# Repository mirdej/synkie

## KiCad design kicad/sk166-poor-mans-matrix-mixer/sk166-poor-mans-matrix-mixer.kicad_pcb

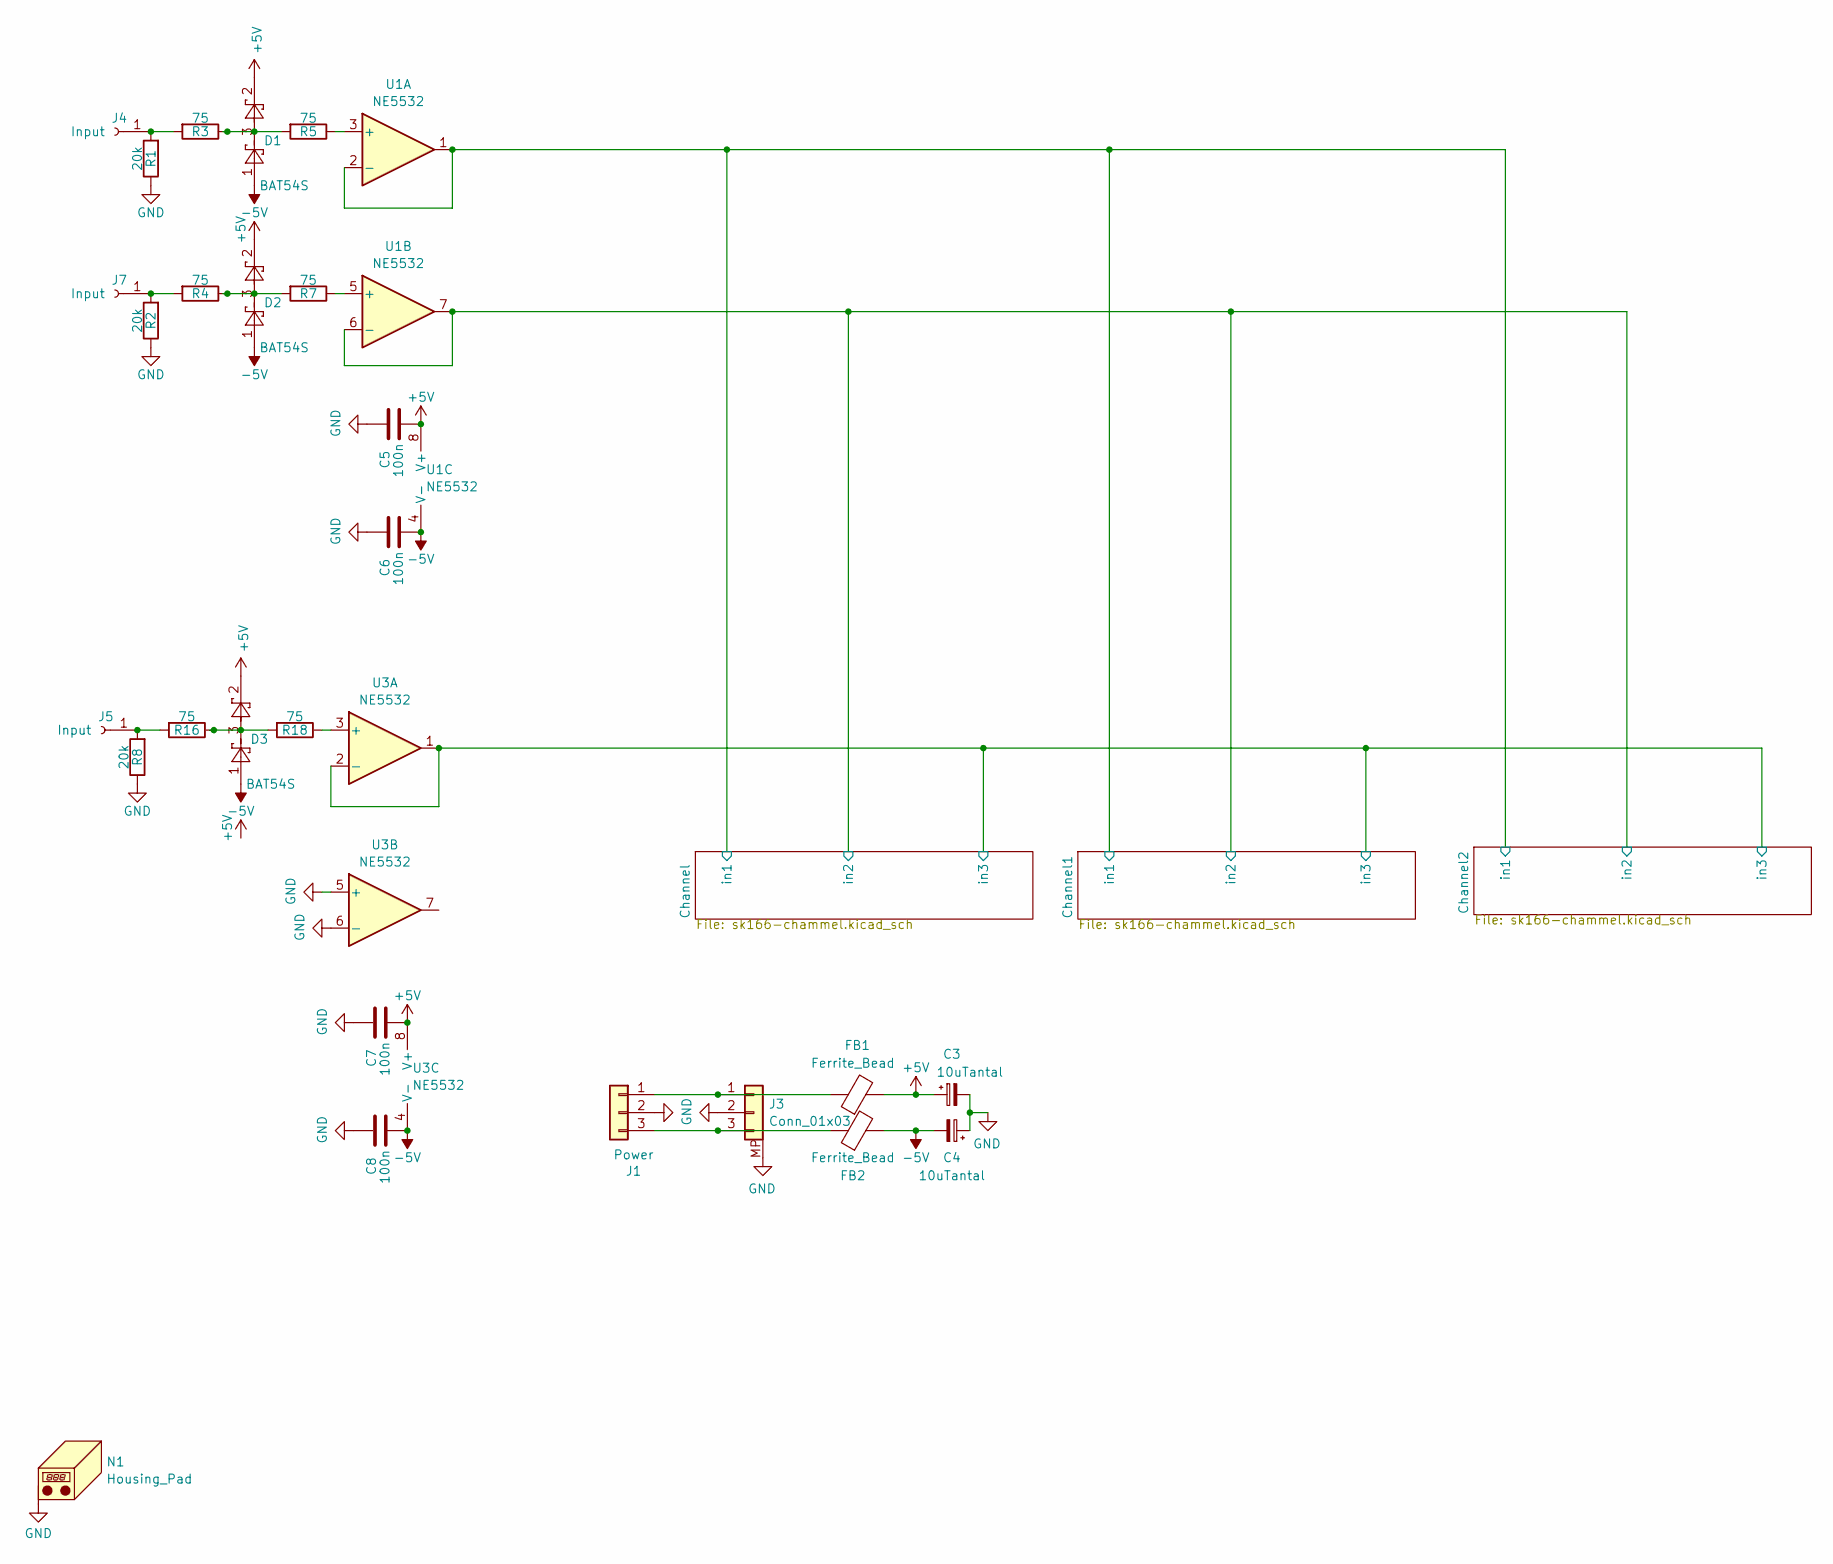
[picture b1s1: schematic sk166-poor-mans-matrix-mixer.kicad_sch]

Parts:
C3, C4: 10uTantal; CP_EIA-3216-18_Kemet-A; LCSC C7171
C5, C6, C7, C8: 100n; C_0603_1608Metric; LCSC C14663
D1, D2, D3: BAT54S; SOT-23; LCSC C7420333
FB1, FB2: Ferrite_Bead; L_0805_2012Metric; LCSC C1017
J1: Power; Molex_KK-254_AE-6410-03A_1x03_P2.54mm_Vertical_SMD
J3: Conn_01x03; Molex_PicoBlade_53398-0371_1x03-1MP_P1.25mm_Vertical; LCSC C293633
J4, J5, J7: Input; Banana2mm-Löthülse
N1: Housing_Pad; Frontplate_40mm
R1, R2, R8: 20k; R_0603_1608Metric; LCSC C4184
R3, R4, R5, R7, R16, R18: 75; R_0603_1608Metric; LCSC C4275
U1, U3: NE5532; SOIC-8_3.9x4.9mm_P1.27mm; LCSC C7426

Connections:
+5V: C3.1, C5.2, C7.2, D1.2, D2.2, D3.2, FB1.2, U1.8 (V+), U3.8 (V+); also elsewhere on the board
-5V: C4.2, C6.2, C8.2, D1.1, D2.1, D3.1, FB2.2, U1.4 (V-), U3.4 (V-); also elsewhere on the board
/Channel/in1: U1.1, U1.2 (-); also elsewhere on the board
/Channel/in2: U1.6 (-), U1.7; also elsewhere on the board
/Channel/in3: U3.1, U3.2 (-); also elsewhere on the board
GND: C3.2, C4.1, C5.1, C6.1, C7.1, C8.1, J1.2, J3.2, J3.MP, N1.1 (PAD_1), R1.1, R2.1, R8.1, U3.5 (+), U3.6 (-); also elsewhere on the board
unnamed: D1.3, R3.1, R5.2
unnamed: D2.3, R4.1, R7.2
unnamed: D3.3, R16.1, R18.2
unnamed: FB1.1, J1.1, J3.1
unnamed: FB2.1, J1.3, J3.3
unnamed: J4.1 (Pin_1_1), R1.2, R3.2
unnamed: J5.1 (Pin_1_1), R8.2, R16.2
unnamed: J7.1 (Pin_1_1), R2.2, R4.2
unnamed: R5.1, U1.3 (+)
unnamed: R7.1, U1.5 (+)
unnamed: R18.1, U3.3 (+)

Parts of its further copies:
C12: 100n; C_0603_1608Metric; LCSC C14663
R26: 75; R_0603_1608Metric; LCSC C4275

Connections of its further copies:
-5V: C12.2; also elsewhere on the board
GND: C12.1; also elsewhere on the board
unnamed 14: R26.1; also elsewhere on the board
unnamed 26: R26.2; also elsewhere on the board

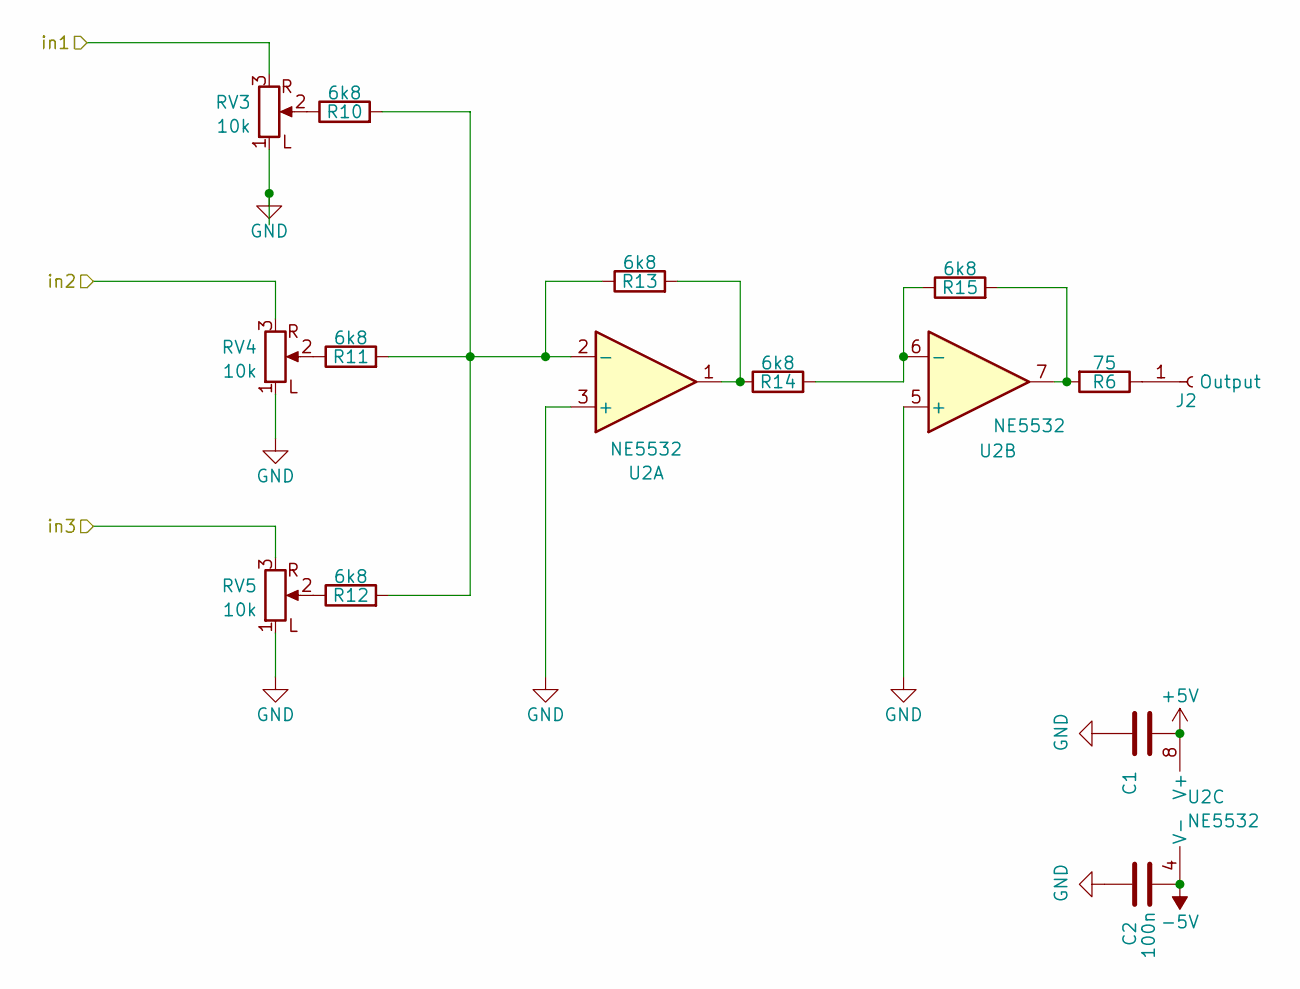
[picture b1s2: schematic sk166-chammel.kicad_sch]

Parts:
C1, C2: 100n; C_0402_1005Metric; LCSC C1525
J2: Output; Banana2mm-Löthülse
R6: 75; R_0603_1608Metric; LCSC C4275
R10, R11, R12, R13, R14, R15: 6k8; R_0603_1608Metric; LCSC C23212
RV3, RV4, RV5: 10k; Alps_RK097_Frontplate; LCSC C115340
U2: NE5532; SOIC-8_3.9x4.9mm_P1.27mm; LCSC C7426

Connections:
+5V: C1.2, U2.8 (V+); also elsewhere on the board
-5V: C2.2, U2.4 (V-); also elsewhere on the board
/Channel/in1: RV3.3; also elsewhere on the board
/Channel/in2: RV4.3; also elsewhere on the board
/Channel/in3: RV5.3; also elsewhere on the board
GND: C1.1, C2.1, RV3.1 (L), RV4.1 (L), RV5.1 (L), U2.3 (+), U2.5 (+); also elsewhere on the board
unnamed: J2.1 (Pin_1_1), R6.1
unnamed: R10.1, RV3.2
unnamed: R11.1, RV4.2
unnamed: R12.1, RV5.2
unnamed: R13.2, R14.1, U2.1
unnamed: R6.2, R15.2, U2.7
unnamed: R10.2, R11.2, R12.2, R13.1, U2.2 (-)
unnamed: R14.2, R15.1, U2.6 (-)

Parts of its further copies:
C9, C10, C11, C12: 100n; C_0402_1005Metric; LCSC C1525
J6, J9: Output; Banana2mm-Löthülse
R20, R21, R22, R23, R24, R25, R27, R28, R29, R30, R31, R32: 6k8; R_0603_1608Metric; LCSC C23212
R26, R33: 75; R_0603_1608Metric; LCSC C4275
RV6, RV7, RV8, RV9, RV10, RV11: 10k; Alps_RK097_Frontplate; LCSC C115340
U4, U5: NE5532; SOIC-8_3.9x4.9mm_P1.27mm; LCSC C7426

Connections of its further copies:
+5V: C9.2, C11.2, U4.8 (V+), U5.8 (V+); also elsewhere on the board
-5V: C10.2, C12.2, U4.4 (V-), U5.4 (V-); also elsewhere on the board
/Channel/in1: RV6.3, RV9.3; also elsewhere on the board
/Channel/in2: RV7.3, RV10.3; also elsewhere on the board
/Channel/in3: RV8.3, RV11.3; also elsewhere on the board
GND: C9.1, C10.1, C11.1, C12.1, RV6.1 (L), RV7.1 (L), RV8.1 (L), RV9.1 (L), RV10.1 (L), RV11.1 (L), U4.3 (+), U4.5 (+), U5.3 (+), U5.5 (+); also elsewhere on the board
unnamed: J6.1 (Pin_1_1), R26.1
unnamed: J9.1 (Pin_1_1), R33.1
unnamed: R20.1, RV6.2
unnamed: R21.1, RV7.2
unnamed: R22.1, RV8.2
unnamed: R23.2, R24.1, U4.1
unnamed: R25.2, R26.2, U4.7
unnamed: R27.1, RV9.2
unnamed: R28.1, RV10.2
unnamed: R29.1, RV11.2
unnamed: R30.2, R31.1, U5.1
unnamed: R32.2, R33.2, U5.7
unnamed: R20.2, R21.2, R22.2, R23.1, U4.2 (-)
unnamed: R24.2, R25.1, U4.6 (-)
unnamed: R27.2, R28.2, R29.2, R30.1, U5.2 (-)
unnamed: R31.2, R32.1, U5.6 (-)

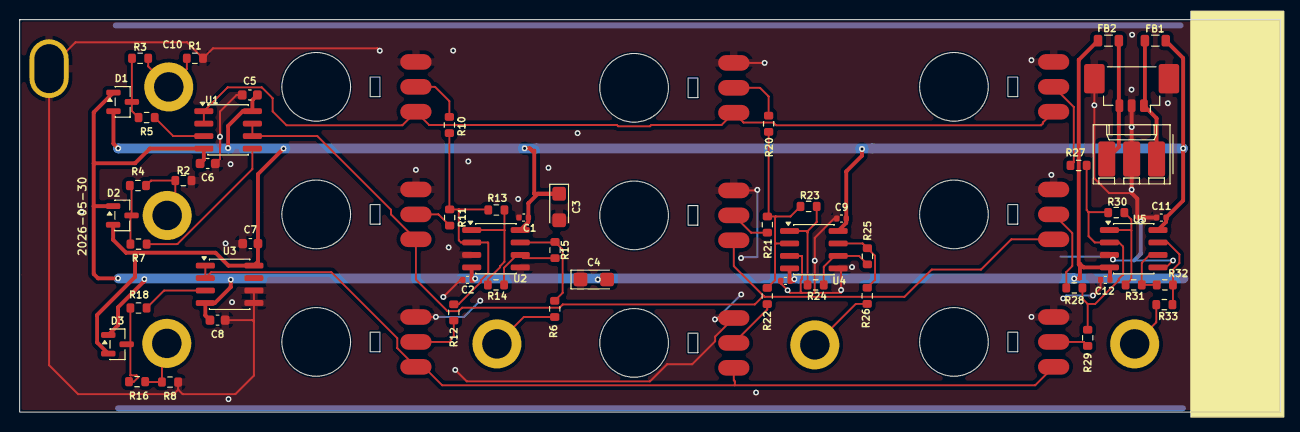
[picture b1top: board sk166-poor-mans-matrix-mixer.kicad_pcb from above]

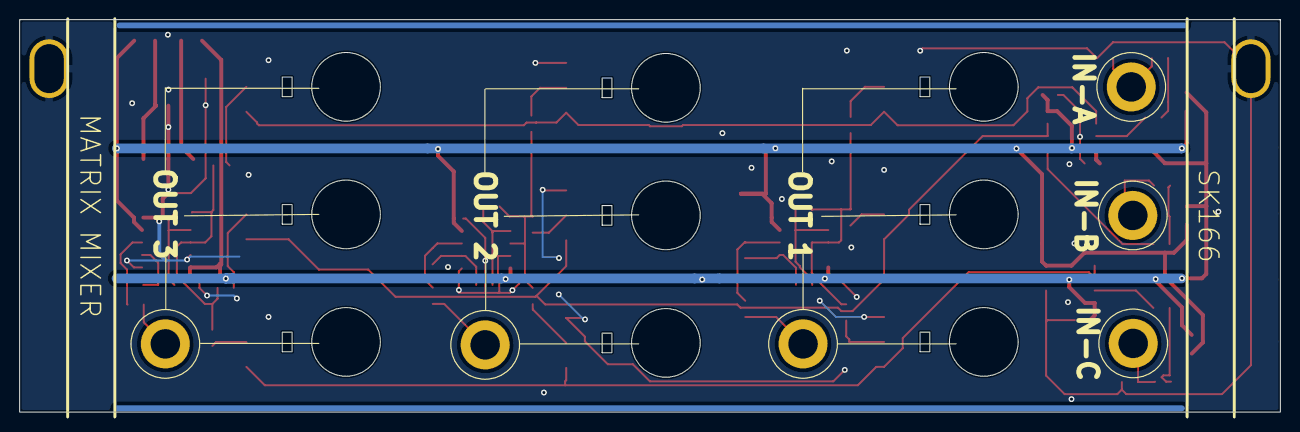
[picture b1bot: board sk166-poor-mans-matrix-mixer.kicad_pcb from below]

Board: 2 copper layers, 128.5 x 40.0 mm, 70 parts (16 on the bottom side), 41 nets.

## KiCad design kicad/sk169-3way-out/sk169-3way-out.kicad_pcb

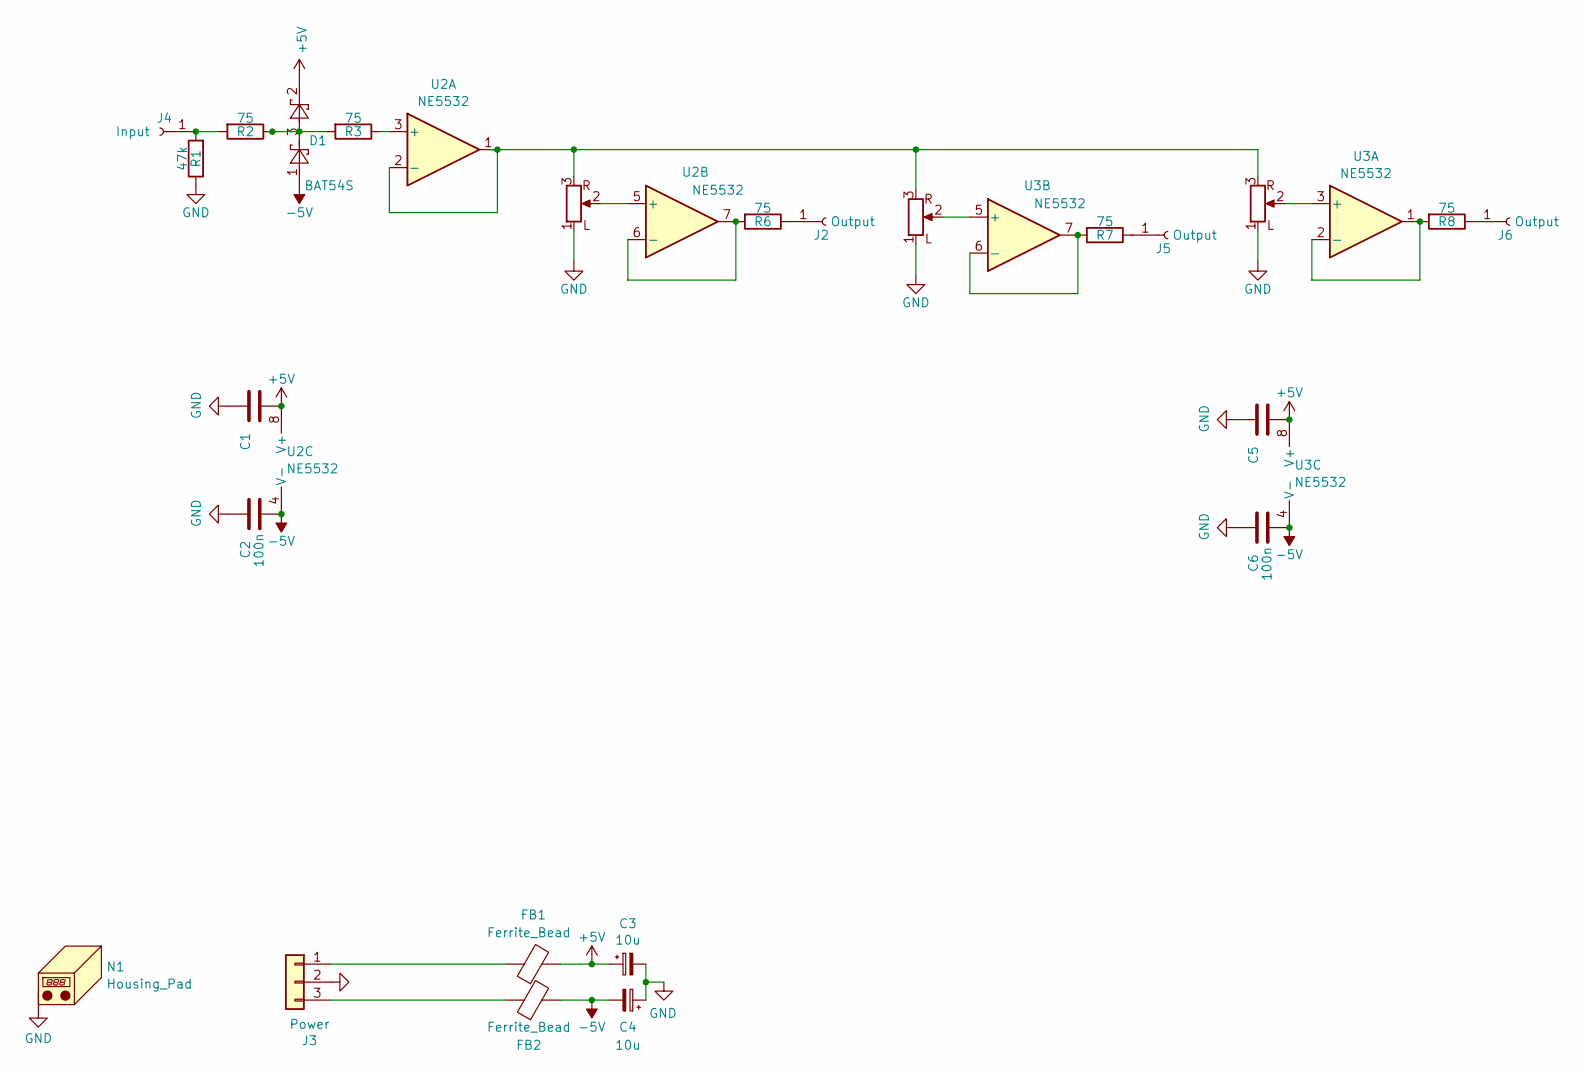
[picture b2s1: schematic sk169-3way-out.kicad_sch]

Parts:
C1, C2, C5, C6: 100n; C_0402_1005Metric; LCSC C1525
C3, C4: 10u; C_0805_2012Metric; LCSC C15850
D1: BAT54S; SOT-23; LCSC C8592
FB1, FB2: Ferrite_Bead; L_0805_2012Metric; LCSC C1017
J2, J5, J6: Output; Banana2mm-Löthülse
J3: Power; Molex_KK-254_AE-6410-03A_1x03_P2.54mm_Vertical_SMD
J4: Input; Banana2mm-Löthülse
N1: Housing_Pad; Frontplate_10mm
R1: 47k; R_0603_1608Metric; LCSC C25819
R2, R3, R6, R7, R8: 75; R_0603_1608Metric; LCSC C4275
RV3, RV4, RV5: 10k; Alps_RK097_Frontplate
U2, U3: NE5532; SOIC-8_3.9x4.9mm_P1.27mm; LCSC C7426

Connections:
+5V: C1.2, C3.1, C5.2, D1.2, FB1.2, U2.8 (V+), U3.8 (V+)
-5V: C2.2, C4.2, C6.2, D1.1, FB2.2, U2.4 (V-), U3.4 (V-)
GND: C1.1, C2.1, C3.2, C4.1, C5.1, C6.1, J3.2, N1.1 (PAD_1), R1.1, RV3.1 (L), RV4.1 (L), RV5.1 (L)
unnamed: D1.3, R2.1, R3.2
unnamed: J2.1 (Pin_1_1), R6.1
unnamed: FB1.1, J3.1
unnamed: FB2.1, J3.3
unnamed: J4.1 (Pin_1_1), R1.2, R2.2
unnamed: J5.1 (Pin_1_1), R7.1
unnamed: J6.1 (Pin_1_1), R8.1
unnamed: R3.1, U2.3 (+)
unnamed: RV3.3, RV4.3, RV5.3, U2.1, U2.2 (-)
unnamed: RV3.2, U2.5 (+)
unnamed: R6.2, U2.6 (-), U2.7
unnamed: RV5.2, U3.3 (+)
unnamed: R8.2, U3.1, U3.2 (-)
unnamed: RV4.2, U3.5 (+)
unnamed: R7.2, U3.6 (-), U3.7

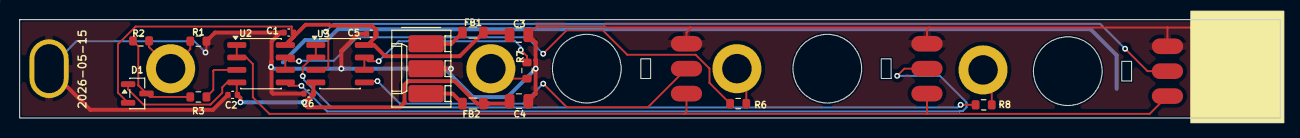
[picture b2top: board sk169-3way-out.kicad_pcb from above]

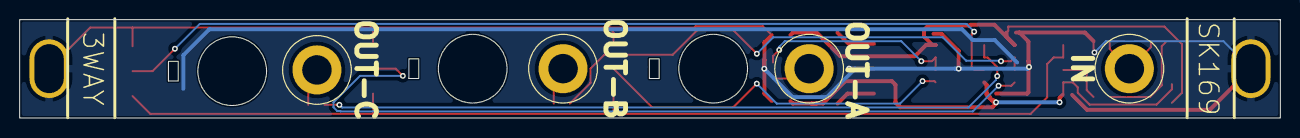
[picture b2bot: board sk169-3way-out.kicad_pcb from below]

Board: 2 copper layers, 128.5 x 10.0 mm, 26 parts (8 on the bottom side), 18 nets.

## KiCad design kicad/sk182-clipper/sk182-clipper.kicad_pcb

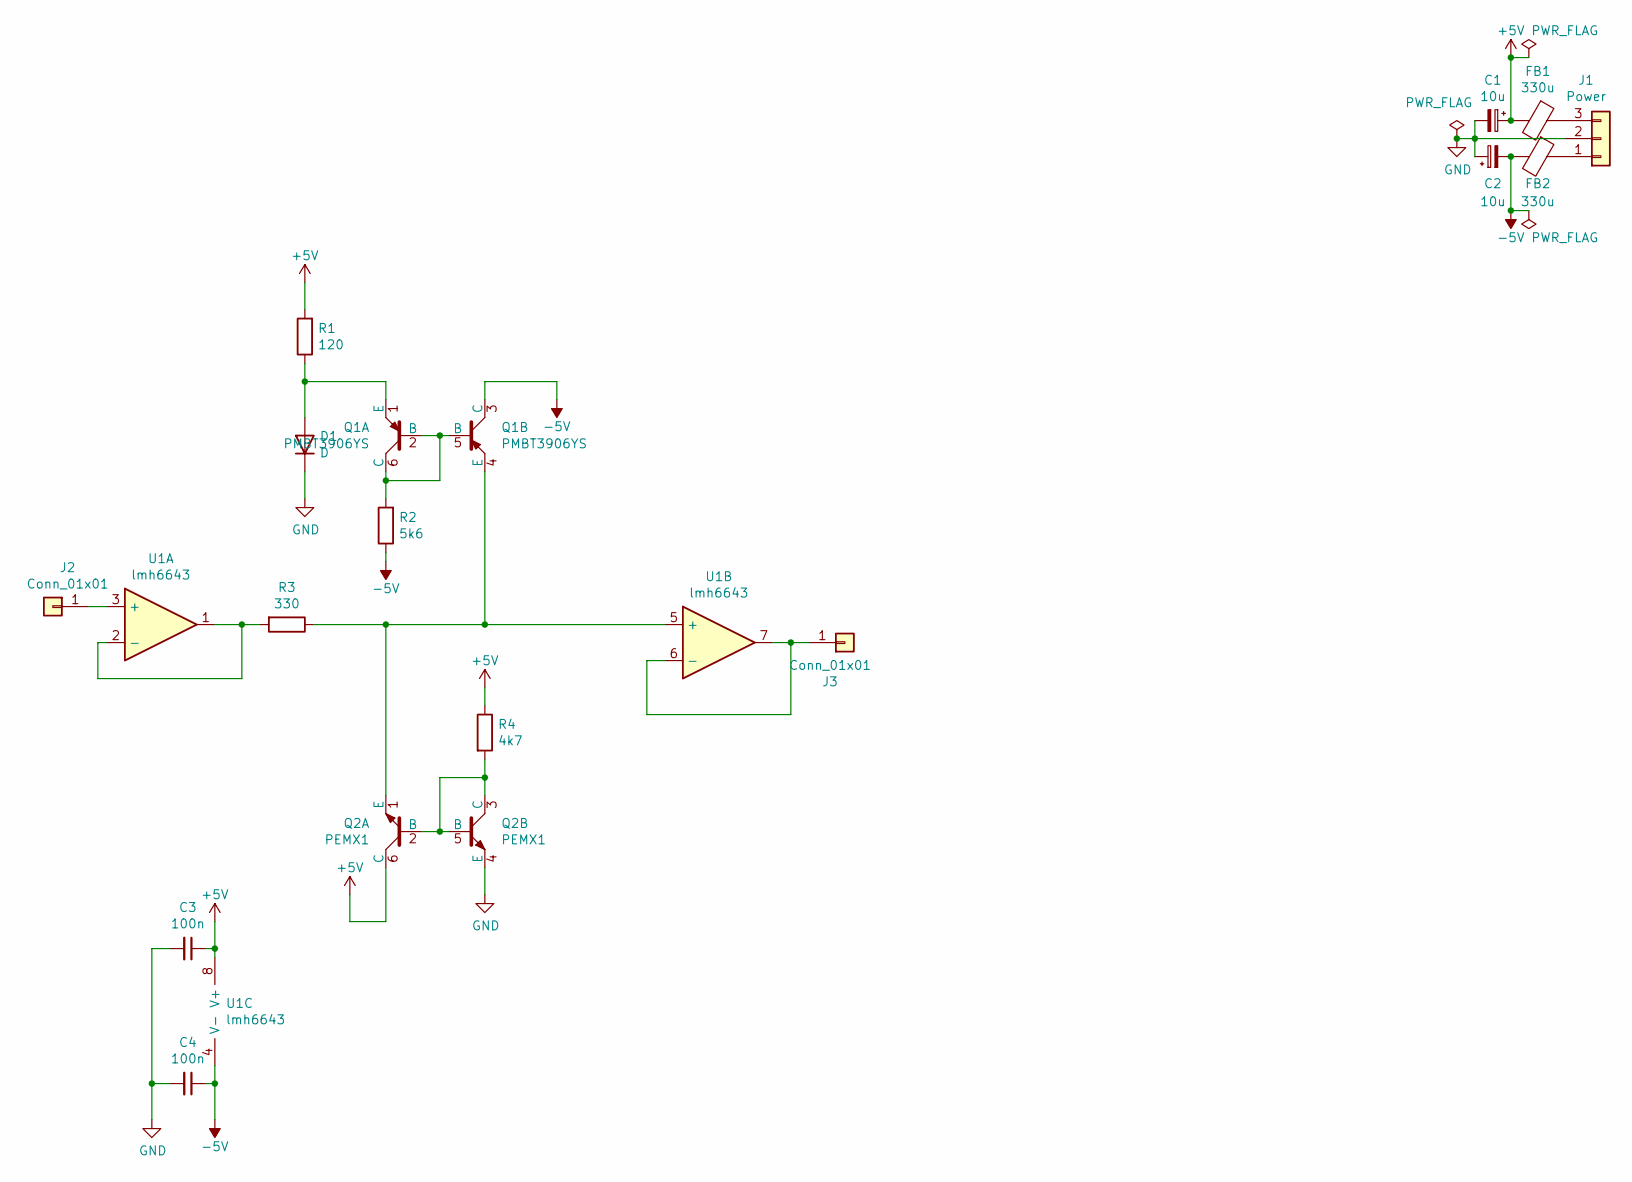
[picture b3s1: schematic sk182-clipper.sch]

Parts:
C1, C2: 10u; CP_EIA-3528-21_Kemet-B_Pad1.50x2.35mm_HandSolder
C3, C4: 100n; C_0805_2012Metric_Pad1.15x1.40mm_HandSolder
D1: D; D_MiniMELF_Handsoldering
FB1, FB2: 330u; L_1206_3216Metric_Pad1.42x1.75mm_HandSolder
J1: Power; Molex_KK-254_AE-6410-03A_1x03_P2.54mm_Vertical
J2, J3: Conn_01x01; Solderpad_1mm
Q1: PMBT3906YS; SOT-363_SC-70-6_Handsoldering
Q2: PEMX1; SOT-666
R1: 120; R_0805_2012Metric_Pad1.15x1.40mm_HandSolder
R2: 5k6; R_0805_2012Metric_Pad1.15x1.40mm_HandSolder
R3: 330; R_0805_2012Metric_Pad1.15x1.40mm_HandSolder
R4: 4k7; R_0805_2012Metric_Pad1.15x1.40mm_HandSolder
U1: lmh6643; SOIC-8_3.9x4.9mm_P1.27mm

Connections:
+5V: C1.1, C3.1, FB1.2, Q2.6 (C), R1.2, R4.1, U1.8 (V+)
-5V: C2.2, C4.1, FB2.2, Q1.3 (C), R2.1, U1.4 (V-)
GND: C1.2, C2.1, C3.2, C4.2, D1.1 (K), J1.2, Q2.4 (E); also elsewhere on the board
unnamed: D1.2 (A), Q1.1 (E), R1.1
unnamed 4: Q2.2 (B), Q2.3 (C), Q2.5 (B), R4.2; also elsewhere on the board
unnamed: FB1.1, J1.3
unnamed: FB2.1, J1.1
unnamed: J2.1, U1.3 (+)
unnamed: J3.1, U1.6 (-), U1.7
unnamed: Q1.2 (B), Q1.5 (B), Q1.6 (C), R2.2
unnamed: Q1.4 (E), Q2.1 (E), R3.1, U1.5 (+)
unnamed: R3.2, U1.1, U1.2 (-)

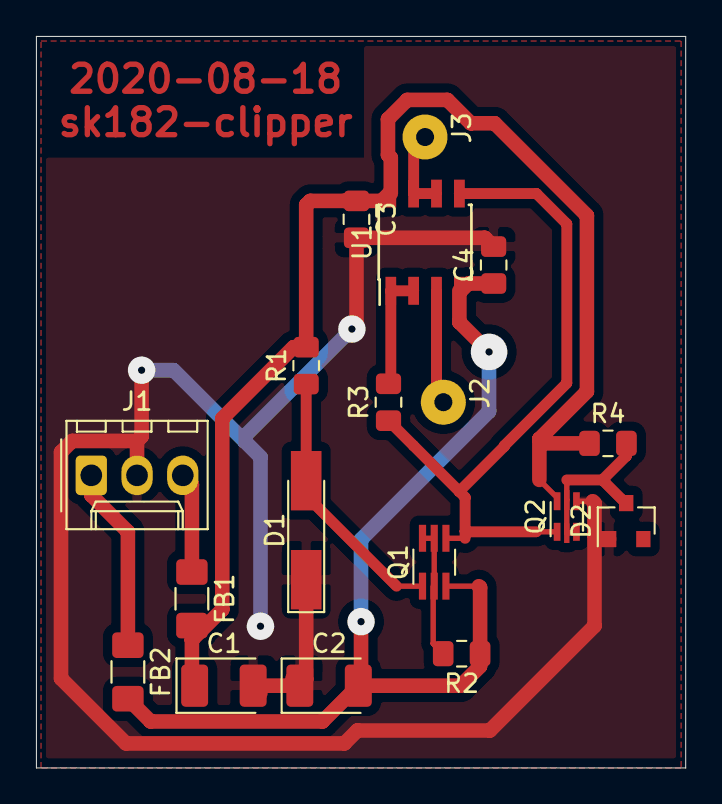
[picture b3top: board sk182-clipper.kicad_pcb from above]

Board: 2 copper layers, 36.1 x 40.6 mm, 18 parts (0 on the bottom side), 12 nets.

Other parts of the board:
D2: BAT54; D_SOT-23_ANK

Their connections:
GND: D2.2; also elsewhere on the board
unnamed 4: D2.1; also elsewhere on the board

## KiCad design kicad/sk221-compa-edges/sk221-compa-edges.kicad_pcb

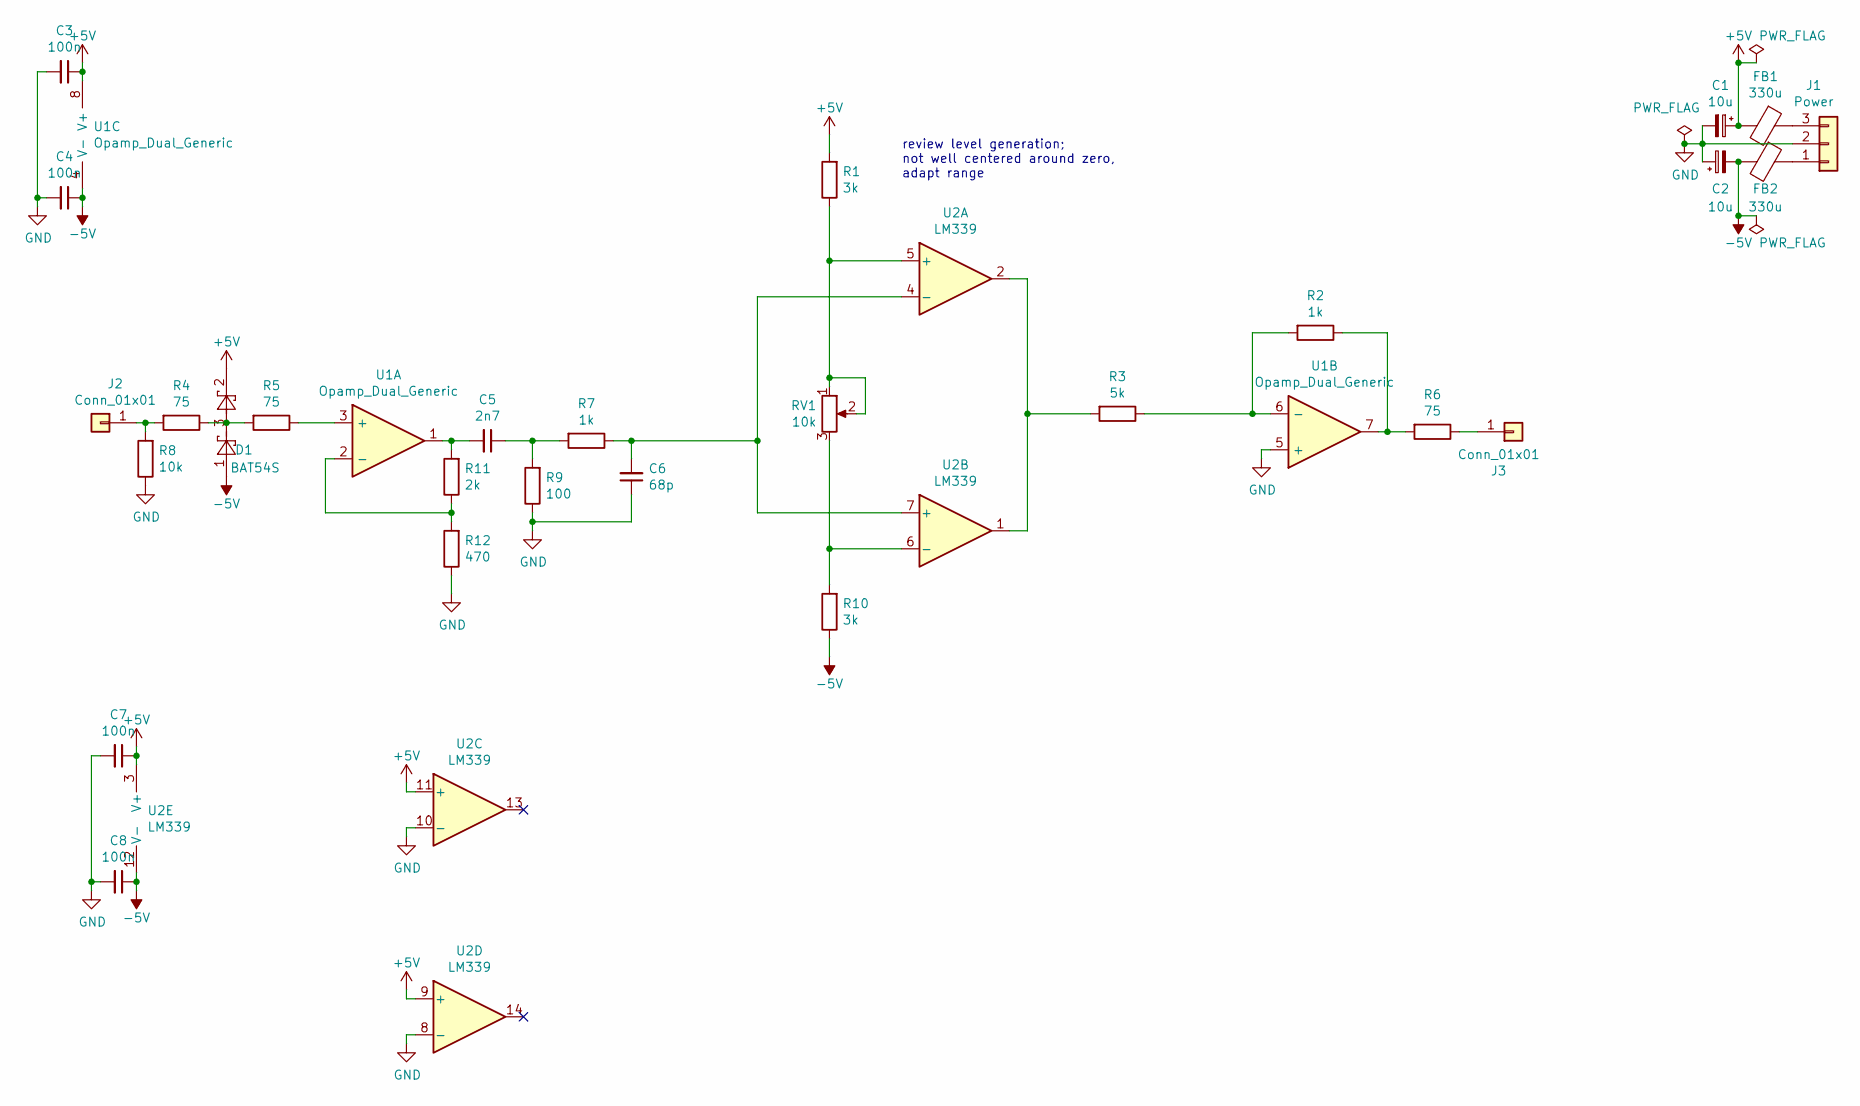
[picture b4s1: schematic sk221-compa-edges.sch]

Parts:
C1, C2: 10u; CP_EIA-3528-21_Kemet-B_Pad1.50x2.35mm_HandSolder
C3, C4, C7, C8: 100n; C_0603_1608Metric_Pad1.05x0.95mm_HandSolder
C5: 2n7; C_0805_2012Metric_Pad1.15x1.40mm_HandSolder
C6: 68p; C_0805_2012Metric_Pad1.15x1.40mm_HandSolder
D1: BAT54S; SOT-23
FB1, FB2: 330u; L_1206_3216Metric_Pad1.42x1.75mm_HandSolder
J1: Power; Molex_KK-254_AE-6410-03A_1x03_P2.54mm_Vertical
J2, J3: Conn_01x01; Solderpad_1mm
R1, R10: 3k; R_0805_2012Metric_Pad1.15x1.40mm_HandSolder
R2, R7: 1k; R_0805_2012Metric_Pad1.15x1.40mm_HandSolder
R3: 5k; R_0805_2012Metric_Pad1.15x1.40mm_HandSolder
R4, R5, R6: 75; R_0805_2012Metric_Pad1.15x1.40mm_HandSolder
R8: 10k; R_0805_2012Metric_Pad1.15x1.40mm_HandSolder
R9: 100; R_0805_2012Metric_Pad1.15x1.40mm_HandSolder
R11: 2k; R_0805_2012Metric_Pad1.15x1.40mm_HandSolder
R12: 470; R_0805_2012Metric_Pad1.15x1.40mm_HandSolder
RV1: 10k; Potentiometer_Alps_RK09Y11_Single_Horizontal
U1: Opamp_Dual_Generic; SOIC-8_3.9x4.9mm_P1.27mm
U2: LM339; SOIC-14_3.9x8.7mm_P1.27mm

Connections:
+5V: C1.1, C3.1, C7.1, D1.2, FB1.2, R1.2, U1.8 (V+), U2.3 (V+), U2.9 (+), U2.11 (+)
-5V: C2.2, C4.1, C8.1, D1.1, FB2.2, R10.1, U1.4 (V-), U2.12 (V-)
GND: C1.2, C2.1, C3.2, C4.2, C6.1, C7.2, C8.2, J1.2, R8.1, R9.1, R12.1, U1.5 (+), U2.8 (-), U2.10 (-)
unnamed: C5.1, R7.2, R9.2
unnamed: C5.2, R11.2, U1.1
unnamed: C6.2, R7.1, U2.4 (-), U2.7 (+)
unnamed: D1.3, R4.1, R5.2
unnamed: FB1.1, J1.3
unnamed: FB2.1, J1.1
unnamed: J2.1, R4.2, R8.2
unnamed: J3.1, R6.1
unnamed: R1.1, RV1.1, RV1.2, U2.5 (+)
unnamed: R2.1, R6.2, U1.7
unnamed: R2.2, R3.1, U1.6 (-)
unnamed: R3.2, U2.1, U2.2
unnamed: R5.1, U1.3 (+)
unnamed: R10.2, RV1.3, U2.6 (-)
unnamed: R11.1, R12.2, U1.2 (-)

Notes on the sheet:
review level generation; not well centered around zero, adapt range

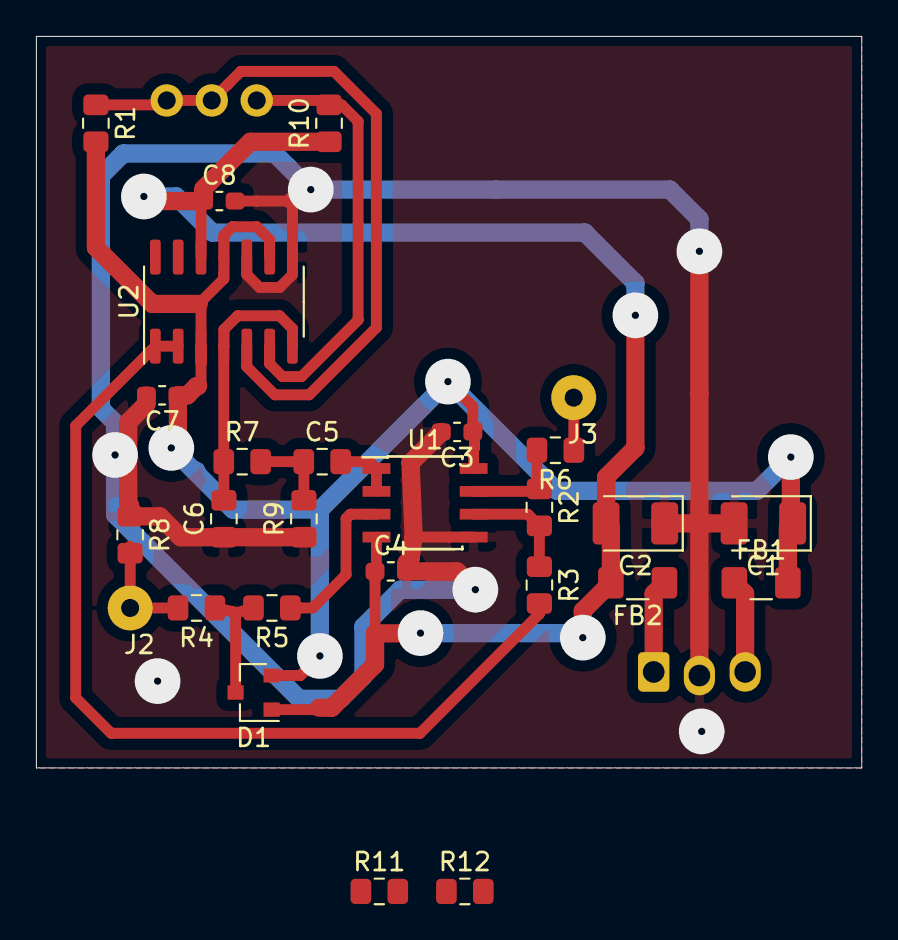
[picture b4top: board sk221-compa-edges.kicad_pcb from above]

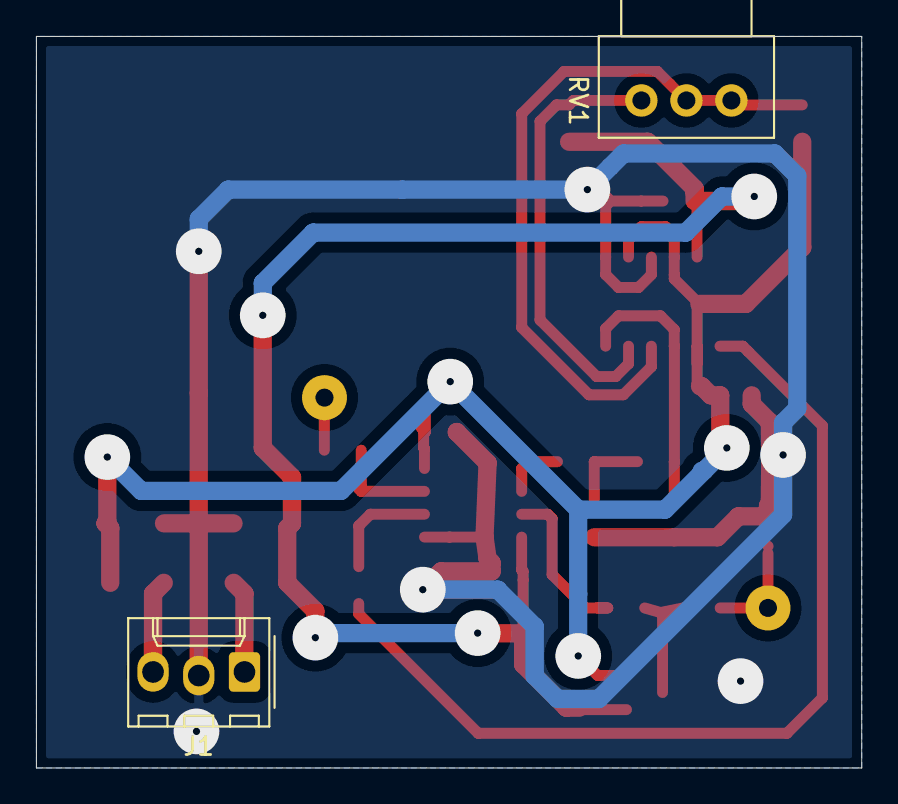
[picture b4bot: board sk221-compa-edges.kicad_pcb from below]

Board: 2 copper layers, 45.8 x 40.6 mm, 29 parts (2 on the bottom side), 18 nets.

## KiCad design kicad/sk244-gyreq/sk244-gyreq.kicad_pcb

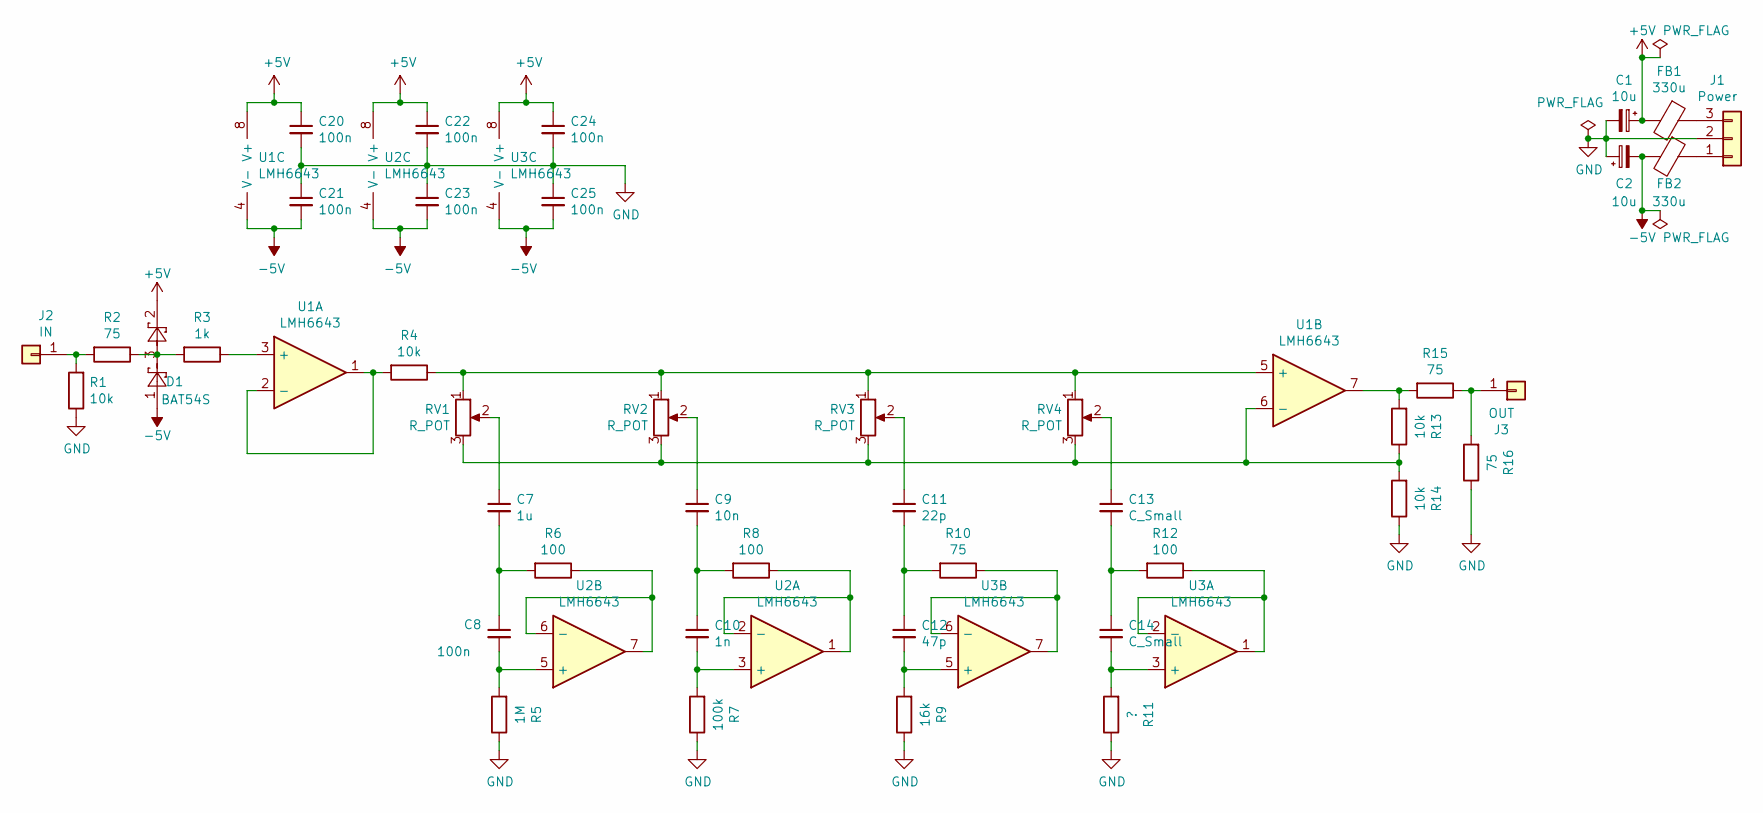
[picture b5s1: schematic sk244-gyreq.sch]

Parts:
C1, C2: 10u; CP_EIA-3528-21_Kemet-B_Pad1.50x2.35mm_HandSolder
C7: 1u; C_0805_2012Metric_Pad1.15x1.40mm_HandSolder
C8, C20, C21, C22, C23, C24, C25: 100n; C_0805_2012Metric_Pad1.15x1.40mm_HandSolder
C9: 10n; C_0805_2012Metric_Pad1.15x1.40mm_HandSolder
C10: 1n; C_0805_2012Metric_Pad1.15x1.40mm_HandSolder
C11: 22p; C_0805_2012Metric_Pad1.15x1.40mm_HandSolder
C12: 47p; C_0805_2012Metric_Pad1.15x1.40mm_HandSolder
C13, C14: C_Small; C_0805_2012Metric_Pad1.15x1.40mm_HandSolder
D1: BAT54S; SOT-23
FB1, FB2: 330u; L_1206_3216Metric_Pad1.42x1.75mm_HandSolder
J1: Power; Molex_KK-254_AE-6410-03A_1x03_P2.54mm_Vertical
J2: IN; Solderpad_1mm
J3: OUT; Solderpad_1mm
R1, R4, R13, R14: 10k; R_0805_2012Metric_Pad1.15x1.40mm_HandSolder
R2, R10, R15, R16: 75; R_0805_2012Metric_Pad1.15x1.40mm_HandSolder
R3: 1k; R_0805_2012Metric_Pad1.15x1.40mm_HandSolder
R5: 1M; R_0805_2012Metric_Pad1.15x1.40mm_HandSolder
R6, R8, R12: 100; R_0805_2012Metric_Pad1.15x1.40mm_HandSolder
R7: 100k; R_0805_2012Metric_Pad1.15x1.40mm_HandSolder
R9: 16k; R_0805_2012Metric_Pad1.15x1.40mm_HandSolder
R11: ?; R_0805_2012Metric_Pad1.15x1.40mm_HandSolder
RV1, RV2, RV3, RV4: R_POT; Potentiometer_Alps_RK09K_Single_Horizontal
U1, U2, U3: LMH6643; SOIC-8_3.9x4.9mm_P1.27mm

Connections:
+5V: C1.1, C20.1, C22.1, C24.1, D1.2, FB1.2, U1.8 (V+), U2.8 (V+), U3.8 (V+)
-5V: C2.2, C21.2, C23.2, C25.2, D1.1, FB2.2, U1.4 (V-), U2.4 (V-), U3.4 (V-)
GND: C1.2, C2.1, C20.2, C21.1, C22.2, C23.1, C24.2, C25.1, J1.2, R1.1, R5.1, R7.1, R9.1, R11.1, R14.1, R16.1
unnamed: C7.1, RV1.2
unnamed: C7.2, C8.1, R6.2
unnamed: C8.2, R5.2, U2.5 (+)
unnamed: C9.1, RV2.2
unnamed: C9.2, C10.1, R8.2
unnamed: C10.2, R7.2, U2.3 (+)
unnamed: C11.1, RV3.2
unnamed: C11.2, C12.1, R10.2
unnamed: C12.2, R9.2, U3.5 (+)
unnamed: C13.1, RV4.2
unnamed: C13.2, C14.1, R12.2
unnamed: C14.2, R11.2, U3.3 (+)
unnamed: D1.3, R2.1, R3.2
unnamed: FB1.1, J1.3
unnamed: FB2.1, J1.1
unnamed: J2.1, R1.2, R2.2
unnamed: J3.1, R15.1, R16.2
unnamed: R3.1, U1.3 (+)
unnamed: R4.1, RV1.1, RV2.1, RV3.1, RV4.1, U1.5 (+)
unnamed: R4.2, U1.1, U1.2 (-)
unnamed: R6.1, U2.6 (-), U2.7
unnamed: R8.1, U2.1, U2.2 (-)
unnamed: R10.1, U3.6 (-), U3.7
unnamed: R12.1, U3.1, U3.2 (-)
unnamed: R13.1, R14.2, RV1.3, RV2.3, RV3.3, RV4.3, U1.6 (-)
unnamed: R13.2, R15.2, U1.7
